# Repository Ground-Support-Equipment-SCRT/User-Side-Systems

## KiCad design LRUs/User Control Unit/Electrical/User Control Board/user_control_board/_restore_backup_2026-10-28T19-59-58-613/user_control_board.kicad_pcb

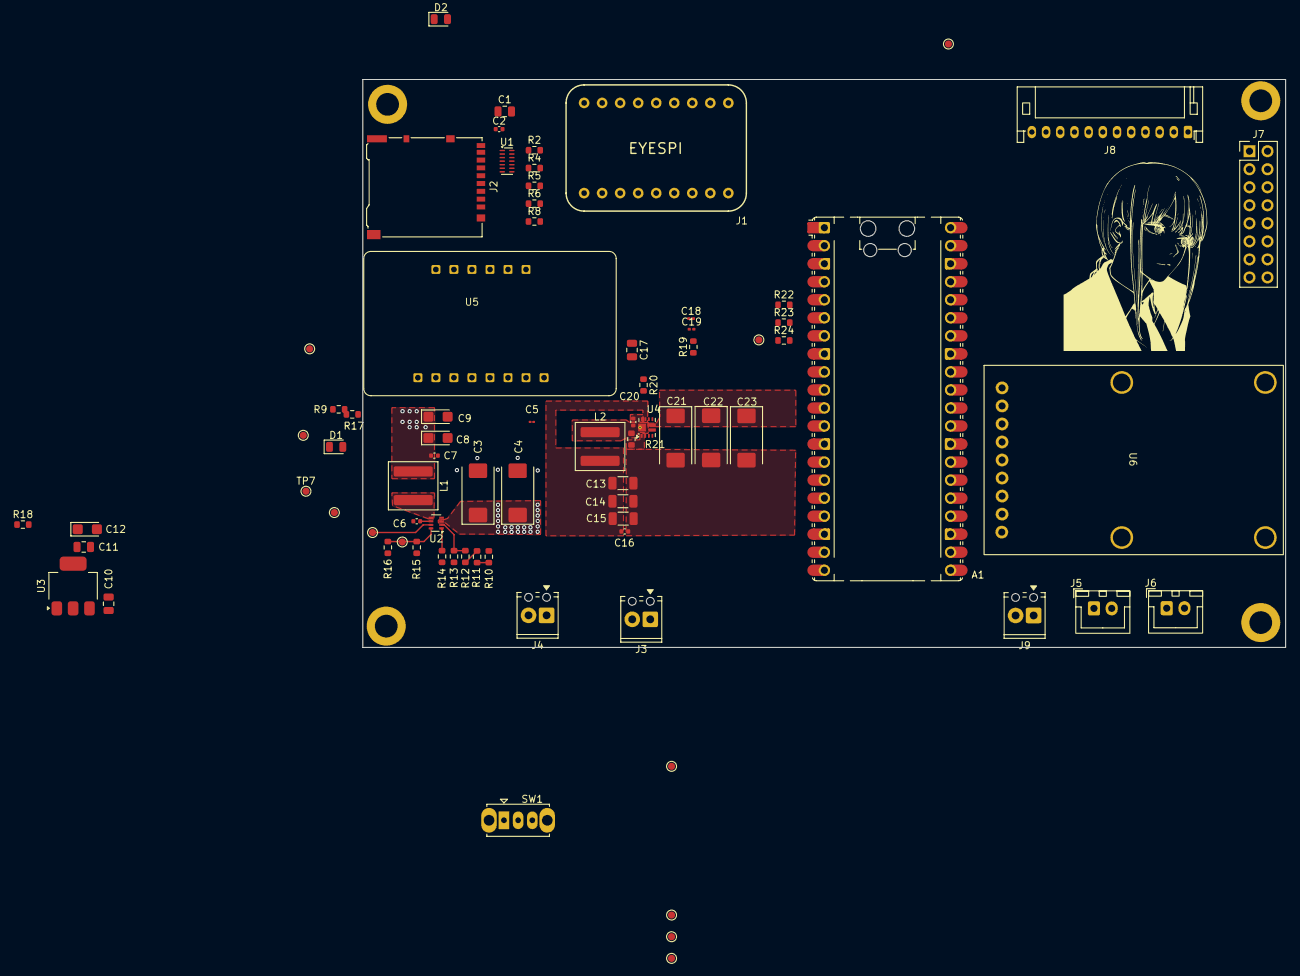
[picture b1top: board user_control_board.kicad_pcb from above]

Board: 4 copper layers, 130.0 x 80.0 mm, 81 parts (0 on the bottom side), 57 nets.

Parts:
A1: RaspberryPi_Pico_W; RaspberryPi_Pico_Common_Unspecified
C1: 10uF; C_0805_2012Metric
C2, C6, C7, C16, C20: 100nF; C_0402_1005Metric
C3, C4, C21, C22, C23: 10uF; CP_EIA-7343-31_Kemet-D
C5: 100nF; C_01005_0402Metric
C8, C9, C12: 10uF; CP_EIA-3216-18_Kemet-A
C10, C11: 1uF; C_0805_2012Metric
C13, C14, C15: 47uF; C_1206_3216Metric
C17: 4.7uF; C_0805_2012Metric
C18: 30pF; C_0201_0603Metric
C19: 680pF; C_0201_0603Metric
D1, D2: GREEN; LED_0805_2012Metric
H1, H2, H3, H4: MountingHole_Pad; MountingHole_3.2mm_M3_ISO14580_Pad
J1: Adafruit EYESPI
J2: Micro_SD_Card_Det2; microSD_HC_Hirose_DM3AT-SF-PEJM5
J3, J4, J9: Screw_Terminal_01x02; TerminalBlock_Phoenix_MPT-0,5-2-2.54_1x02_P2.54mm_Horizontal
J5, J6: B2B-XH-A; JST_XH_B2B-XH-A_1x02_P2.50mm_Vertical
J7: Conn_02x08_Odd_Even; PinHeader_2x08_P2.54mm_Vertical
J8: S12B-PH-K-S; JST_PH_S12B-PH-K_1x12_P2.00mm_Horizontal
L1: 15uH; L_Coilcraft_XAL6060-XXX
L2: 1.2uH; L_Coilcraft_XAL6030-XXX
R2, R5, R6, R14: 0; R_0603_1608Metric
R4: 22; R_0603_1608Metric
R8: 10k; R_0603_1608Metric
R9: 47k; R_0603_1608Metric
R10: 220k; R_0603_1608Metric
R11: 20k; R_0603_1608Metric
R12: 9.1k; R_0603_1608Metric
R13: 51k; R_0603_1608Metric
R15: 68k; R_0603_1608Metric
R16: 13k; R_0603_1608Metric
R17: 2k; R_0603_1608Metric
R18: 220; R_0603_1608Metric
R19: 32.4k; R_0603_1608Metric
R20: 127k; R_0603_1608Metric
R21: 309k; R_0603_1608Metric
R22: 1.05M; R_0603_1608Metric
R23: 100k; R_0603_1608Metric
R24: 18k; R_0603_1608Metric
SW1: SW_SPDT; SW_Slide_SPDT_Straight_CK_OS102011MS2Q
TP1, TP2, TP3, TP4, TP5, TP6, TP7, TP8, TP9, TP10, TP11, TP12: TestPoint; TestPoint_Pad_D1.0mm
U1: TPD6E05U06RVZ; Texas_R-PUSON-N14
U2: TPS62933P; SOT-583-8
U3: AMS1117-3.3; SOT-223-3_TabPin2
U4: TPS61089RNRR; Texas_VQFN-RNR0011A-11
U5: Adafruit PCM510x I2S DAC
U6: Ada_Ethernet

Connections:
+3V3: C1.1, C2.1, C11.1, C12.1, J1.1 (VIN), J2.4 (VDD), J7.1, J8.2, R8.1, R9.1, R18.1, TP1.1 (1_1), TP7.1 (1_1), U3.2 (VO), U5.1 (VIN)
+5V: C7.1, C8.1, C9.1, J8.1, L1.1, R15.1, R17.2, SW1.3 (C), TP5.1 (1_1), U6.1 (VIN)
+12V: C21.1, C22.1, C23.1, J5.1, J6.1, J9.1, R22.1, TP12.1 (1_1), U4.6 (VOUT)
/Power/5V/BST: C6.1, U2.6 (BST)
/Power/5V/FB: R15.2, R16.1, TP6.1 (1_1), U2.8 (FB)
/Power/5V/RT: R14.2, U2.1 (RT)
/Power/5V/SW: C6.2, L1.2, U2.5 (SW)
/Power/5V/VEN: R12.1, R13.1, TP4.1 (1_1), U2.2 (EN)
/Power/12V/VIN: C3.1, C4.1, C5.1, C10.1, C13.1, C14.1, C15.1, C16.1, J4.2, L2.1, R10.2, TP3.1 (1_1), TP8.1 (1_1), U2.3 (VIN), U3.3 (VI), U4.9 (VIN)
ARM_STAT: A1.14 (GPIO10), J8.7
COOL: A1.16 (GPIO12), J8.9
DAC_BCK: A1.31 (GPIO26_ADC0), U5.5 (BCK)
DAC_DIN: A1.34 (GPIO28_ADC2), U5.4 (DIN)
DAC_WSEL: A1.32 (GPIO27_ADC1), U5.3 (WSEL)
ETHERNET_CS: A1.29 (GPIO22), U6.7 (CS)
ETHERNET_IRQ: A1.27 (GPIO21), U6.8 (IRQ)
ETHERNET_RST: A1.26 (GPIO20), U6.9 (RESET)
FILL: A1.19 (GPIO14), J8.11
G0_RADIO: A1.11 (GPIO8), J7.2
GND: A1.3 (GND), A1.8 (GND), A1.13 (GND), A1.18 (GND), A1.23 (GND), A1.28 (GND), A1.33 (AGND), A1.38 (GND), C1.2, C2.2, C3.2, C4.2, C5.2, C7.2, C8.2, C9.2, C10.2, C11.2, C12.2, C13.2, C14.2, C15.2, C16.2, C17.2, C18.2, C19.2, C21.2, C22.2, C23.2, D1.1 (K), D2.1 (K), H1.1 (1_1), H2.1 (1_1), H3.1 (1_1), H4.1 (1_1), J1.3 (GND), J2.6 (VSS), J2.9 (DET_B), J2.SH (SHIELD), J3.2, J5.2, J6.2, J7.8, J8.3, J8.4, J9.2, R13.2, R14.1, R16.2, R20.1, R24.2, TP11.1 (1_1), U1.5 (GND), U1.10 (GND), U2.4 (GND), U3.1 (GND), U4.5 (GND), U5.2 (GND), U5.7 (G), U6.3 (GND)
I2C0_SCL: A1.7 (I2C0_SCL), J1.13 (SCL), J8.6
I2C0_SDA: A1.6 (I2C0_SDA), J1.14 (SDA), J8.5
LAUNCH_STAT: A1.15 (GPIO11), J8.8
LCD_CS: A1.22 (GPIO17), J1.12 (TC_CS)
LCD_DC: A1.1 (GPIO0), J1.7 (DC)
LCD_RESET: A1.2 (GPIO1), J1.8 (RESET)
MISO: A1.21 (GPIO16), J7.5, R5.2, U6.5 (MISO)
MOSI: A1.25 (GPIO19), J1.5 (MOSI), J7.6, R2.2, U6.6 (MOSI)
unnamed: A1.39 (VSYS), SW1.2 (B)
unnamed: C19.1, R19.1
unnamed: D1.2 (A), R17.1
unnamed: D2.2 (A), R18.2
unnamed: J2.5 (CLK), R4.2, U1.11 (D2-)
unnamed: J2.3 (CMD), U1.12 (D2+)
unnamed: J2.7 (DAT0), R5.1, U1.9 (D3+)
unnamed: J2.8 (DAT1), R2.1, U1.8 (D3-)
unnamed: J2.1 (DAT2), U1.14 (D1+)
unnamed: J2.2 (DAT3/CD), R6.1, U1.13 (D1-)
unnamed: J2.10 (DET_A), R8.2
unnamed: J3.1, J4.1
unnamed: R10.1, R11.2
unnamed: R11.1, R12.2
unnamed: R23.2, R24.1
unnamed: C20.1, U4.10 (BOOT)
unnamed: C18.1, R19.2, U4.4 (COMP)
unnamed: C17.1, U4.2 (VCC), U4.7 (EN)
unnamed: R22.2, R23.1, TP10.1 (1_1), U4.3 (FB)
unnamed: R21.1, U4.1 (FSW)
unnamed: R20.2, U4.8 (ILIM)
unnamed: C20.2, L2.2, R21.2, TP9.1 (1_1), U4.11 (SW)
PG: A1.12 (GPIO9), R9.2, TP2.1 (1_1), U2.7 (PG)
RADIO_CS: A1.9 (GPIO6), J1.6 (MISO), J7.3
RADIO_RST: A1.4 (GPIO2), J7.7
SCK: A1.24 (SPI0_SCK), J1.4 (SCK), J7.4, R4.1, U6.4 (SCK)
SD_CS: A1.10 (GPIO7), R6.2
VALVE_ARM: A1.17 (GPIO13), J8.10
VENT: A1.20 (GPIO15), J8.12

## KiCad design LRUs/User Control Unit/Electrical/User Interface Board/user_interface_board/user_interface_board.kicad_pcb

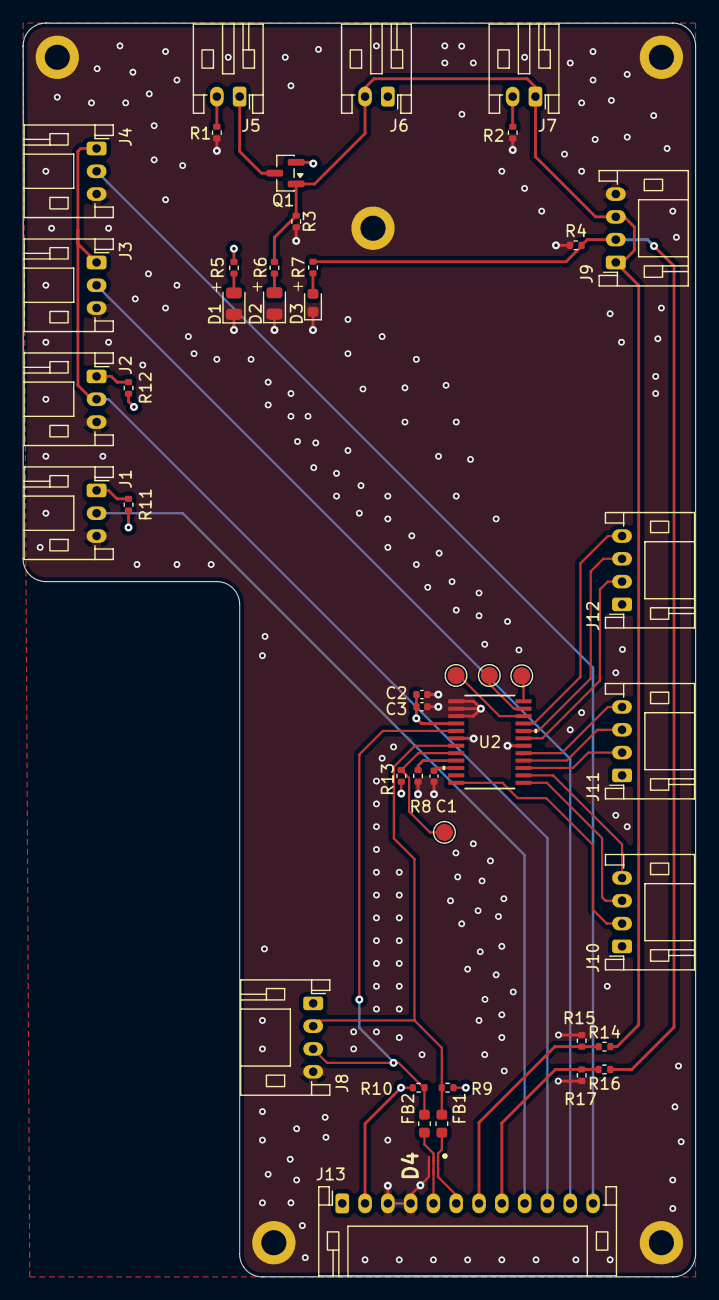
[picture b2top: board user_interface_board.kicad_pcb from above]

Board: 4 copper layers, 59.0 x 110.0 mm, 50 parts (0 on the bottom side), 38 nets.

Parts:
C1, C2: 1uF; C_0402_1005Metric
C3: 0.1uF; C_0402_1005Metric
D1: KT-0805G; LED_0805_2012Metric
D2: KT-0805Y; LED_0805_2012Metric
D3: KT-0603R; LED_0603_1608Metric
D4: RCLAMP0582N(ES); SON40P100X120X65-6N
FB1, FB2: GZ1608D601TF; L_0603_1608Metric
H1, H2, H3, H4, H5: MountingHole_Pad; MountingHole_2.2mm_M2_DIN965_Pad
J1, J2, J3, J4: S3B-PH-K-S; JST_PH_S3B-PH-K_1x03_P2.00mm_Horizontal
J5, J6, J7: S2B-PH-K-S; JST_PH_S2B-PH-K_1x02_P2.00mm_Horizontal
J8, J9, J10, J11, J12: S4B-PH-K-S; JST_PH_S4B-PH-K_1x04_P2.00mm_Horizontal
J13: S12B-PH-K-S; JST_PH_S12B-PH-K_1x12_P2.00mm_Horizontal
Q1: AO3401A; SOT-23
R1, R2, R5, R6: 470; R_0402_1005Metric
R3, R4, R11, R12: 10k; R_0402_1005Metric
R7: 200; R_0402_1005Metric
R8: 12k; R_0402_1005Metric
R9, R10: 4.7k; R_0402_1005Metric
R13: 0; R_0402_1005Metric
R14, R16: 1k; R_0402_1005Metric
R15, R17: 2k; R_0402_1005Metric
TP1: LED_OUT9; TestPoint_Pad_D1.5mm
TP2: LED_OUT10; TestPoint_Pad_D1.5mm
TP3: LED_OUT11; TestPoint_Pad_D1.5mm
TP4: LED_EN; TestPoint_Pad_D1.5mm
U2: LP5012PWR; TSSOP_012PWR_TEX

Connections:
+3V3: C2.1, C3.1, J8.1, J13.2, R9.1, R10.2, R11.1, R12.1, R13.1, U2.4 (VCC)
+5V: J6.1, J10.1, J11.1, J12.1, J13.1, Q1.2 (S), R5.1
/top level/I2C_SCL: D4.1, D4.6, FB1.2, J13.6
/top level/I2C_SDA: D4.2, D4.5, FB2.1, J13.5
/top level/LED driver/OUT0: J10.2, U2.12 (OUT0)
/top level/LED driver/OUT1: J10.3, U2.13 (OUT1)
/top level/LED driver/OUT2: J10.4, U2.14 (OUT2)
/top level/LED driver/OUT3: J11.2, U2.15 (OUT3)
/top level/LED driver/OUT4: J11.3, U2.16 (OUT4)
/top level/LED driver/OUT5: J11.4, U2.17 (OUT5)
/top level/LED driver/OUT6: J12.2, U2.19 (OUT6)
/top level/LED driver/OUT7: J12.3, U2.20 (OUT7)
/top level/LED driver/OUT8: J12.4, U2.21 (OUT8)
/top level/SCL: FB1.1, J8.2, R9.2, U2.7 (SCL)
/top level/SDA: FB2.2, J8.3, R10.1, U2.5 (SDA)
/top level/launch circuit/ARMED_LED+: J6.2, J7.1, J9.1, J9.3, Q1.1 (G), R3.1, R6.1, R14.1
/top level/launch circuit/ARMED_LED-: J7.2, R2.1
/top level/launch circuit/ARMED_STAT: J13.7, R14.2, R15.1
/top level/launch circuit/BUTTON_NO: J9.2, R4.1, R7.1, R16.1
/top level/launch circuit/LAUNCH_STAT: J13.8, R16.2, R17.1
/top level/launch circuit/SAFE_LED+: J5.1, Q1.3 (D)
/top level/launch circuit/SAFE_LED-: J5.2, R1.1
GND: C1.2, C2.2, C3.2, D1.1 (K), D2.1 (K), D3.1 (K), D4.3, D4.4, H1.1 (1_1), H2.1 (1_1), H3.1 (1_1), H4.1 (1_1), H5.1 (1_1), J1.3, J2.3, J3.3, J4.3, J8.4, J9.4, J13.3, J13.4, R1.2, R2.2, R3.2, R4.2, R8.2, R15.2, R17.2, U2.1 (ADDR0), U2.2 (AGND), U2.3 (ADDR1), U2.6 (PGND), U2.18 (DGND)
unnamed: D1.2 (A), R5.2
unnamed: D2.2 (A), R6.2
unnamed: D3.2 (A), R7.2
unnamed: J1.1, R11.2
unnamed: J1.2, J13.9
unnamed: J2.1, R12.2
unnamed: J2.2, J3.1, J4.1, J13.10
unnamed: J3.2, J13.11
unnamed: J4.2, J13.12
unnamed: R13.2, TP4.1 (1_1), U2.8 (EN)
unnamed: R8.1, U2.9 (IREF)
unnamed: TP1.1 (1_1), U2.22 (OUT9)
unnamed: TP2.1 (1_1), U2.23 (OUT10)
unnamed: TP3.1 (1_1), U2.24 (OUT11)
unnamed: C1.1, U2.10 (VCAP)

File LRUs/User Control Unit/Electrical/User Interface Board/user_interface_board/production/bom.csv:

Designator,Footprint,Quantity,Value,LCSC Part #
"C1, C2",0402,2,1uF,C52923
C3,0402,1,0.1uF,C1525
D1,0805,1,KT-0805G,C2297
D2,0805,1,KT-0805Y,C2296
D3,0603,1,KT-0603R,C2286
D4,SON40P100X120X65-6N,1,RCLAMP0582N(ES),
"FB1, FB2",0603,2,GZ1608D601TF,C1002
"J1, J2, J3, J4",JST_PH_S3B-PH-K_1x03_P2.00mm_Horizontal,4,S3B-PH-K-S,
"J10, J11, J12, J8, J9",JST_PH_S4B-PH-K_1x04_P2.00mm_Horizontal,5,S4B-PH-K-S,
J13,JST_PH_S12B-PH-K_1x12_P2.00mm_Horizontal,1,S12B-PH-K-S,
"J5, J6, J7",JST_PH_S2B-PH-K_1x02_P2.00mm_Horizontal,3,S2B-PH-K-S,
Q1,SOT-23,1,AO3401A,
"R1, R2, R5, R6",0402,4,470,C25117
"R11, R12, R3, R4",0402,4,10k,C25744
R13,0402,1,0,C17168
"R14, R16",0402,2,1k,C11702
"R15, R17",0402,2,2k,C4109
R7,0402,1,200,C25087
R8,0402,1,12k,C25752
TP1,TestPoint_Pad_D1.5mm,1,LED_OUT9,
TP2,TestPoint_Pad_D1.5mm,1,LED_OUT10,
TP3,TestPoint_Pad_D1.5mm,1,LED_OUT11,
TP4,TestPoint_Pad_D1.5mm,1,LED_EN,
U2,TSSOP_012PWR_TEX,1,LP5012PWR,
